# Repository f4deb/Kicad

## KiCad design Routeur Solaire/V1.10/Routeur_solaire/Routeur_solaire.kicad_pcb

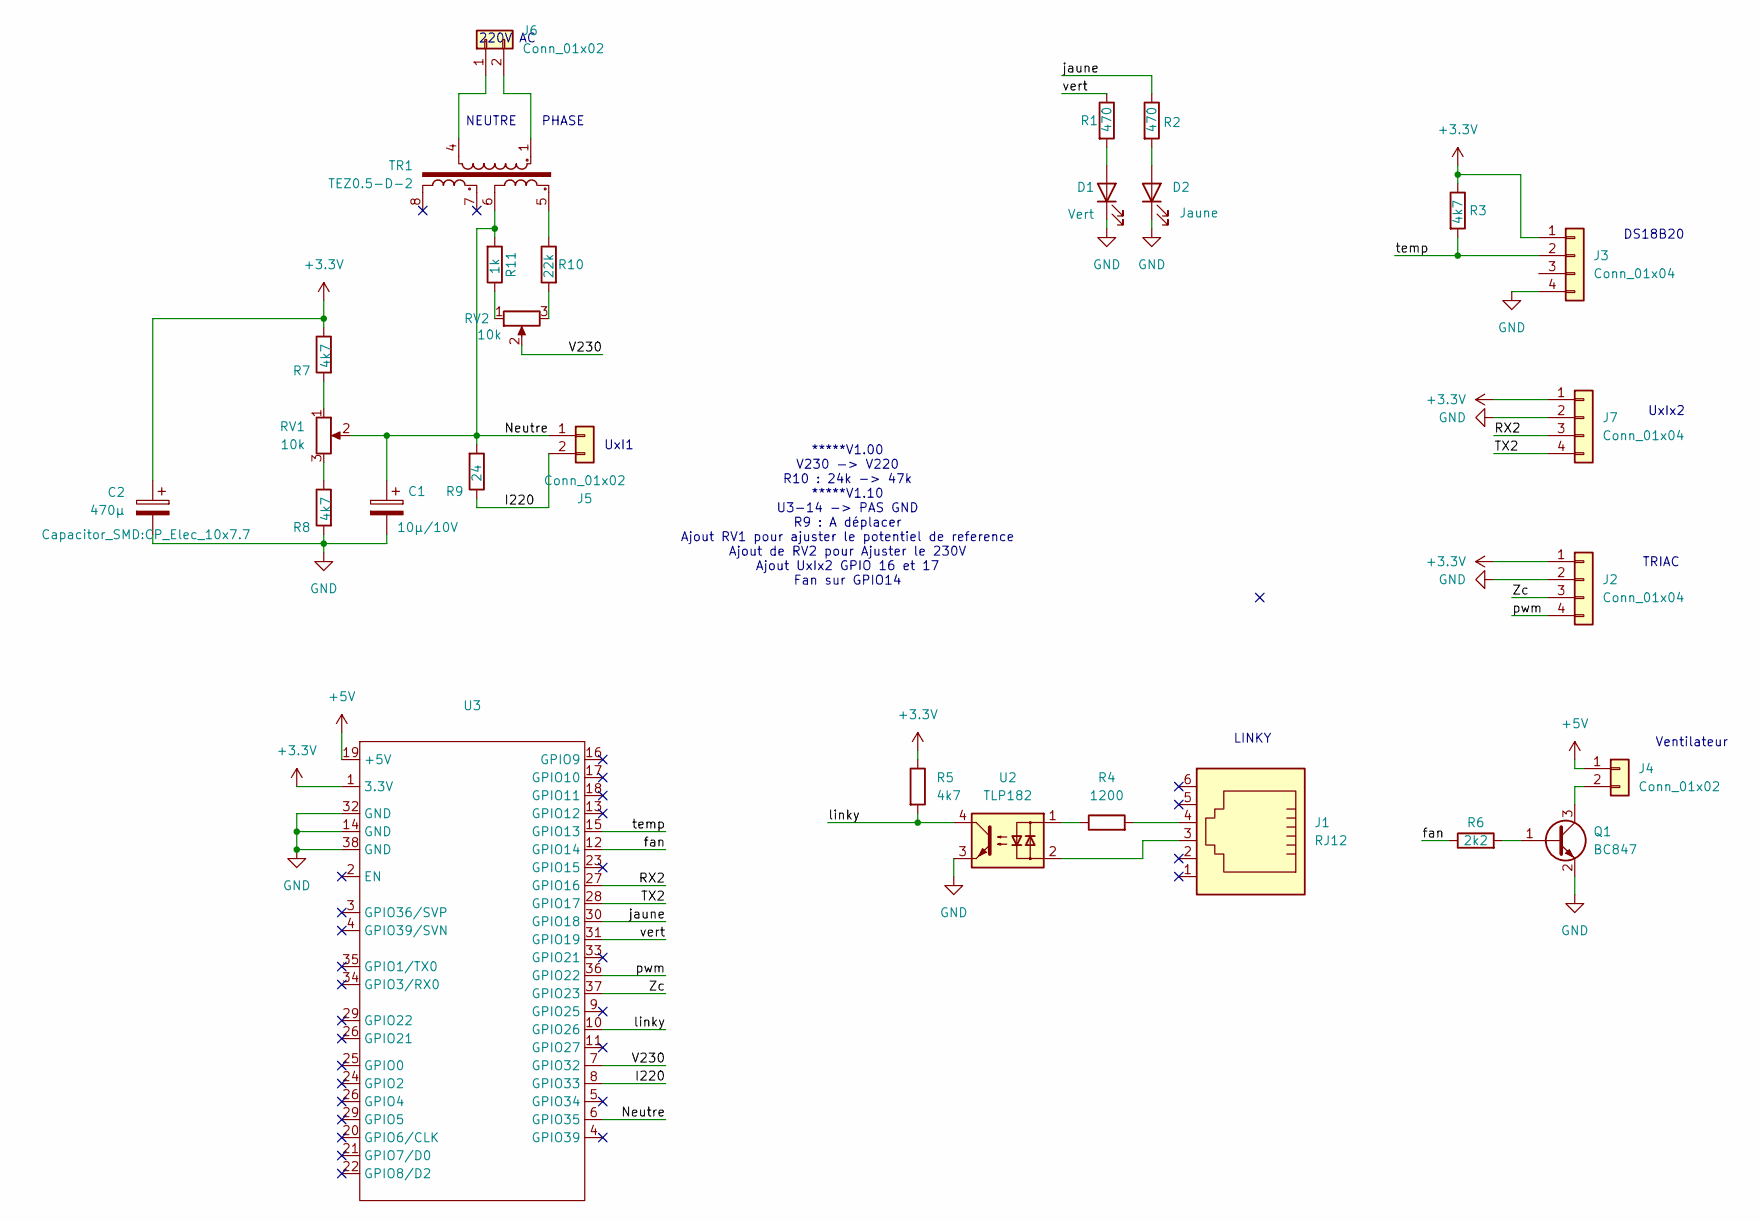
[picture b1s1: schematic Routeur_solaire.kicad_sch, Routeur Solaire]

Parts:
C1: 10µ/10V; CP_Elec_6.3x3
C2: 470µ; CP_Elec_10x7.7
D1: Vert; LED_0805_2012Metric_Pad1.15x1.40mm_HandSolder
D2: Jaune; LED_0805_2012Metric_Pad1.15x1.40mm_HandSolder
J1: RJ12; RJ25_Wayconn_MJEA-660X1_Horizontal
J2, J3, J7: Conn_01x04; PhoenixContact_MCV_1,5_4-G-3.81_1x04_P3.81mm_Vertical
J4, J5: Conn_01x02; PhoenixContact_MCV_1,5_2-G-3.81_1x02_P3.81mm_Vertical
J6: Conn_01x02; PhoenixContact_MSTBVA_2,5_2-G-5,08_1x02_P5.08mm_Vertical
Q1: BC847; SOT-23
R1, R2: 470; R_0603_1608Metric_Pad0.98x0.95mm_HandSolder
R3, R5: 4k7; R_0603_1608Metric_Pad0.98x0.95mm_HandSolder
R4: 1200; R_0805_2012Metric_Pad1.20x1.40mm_HandSolder
R6: 2k2; R_0603_1608Metric_Pad0.98x0.95mm_HandSolder
R7, R8: 4k7; R_0805_2012Metric_Pad1.20x1.40mm_HandSolder
R9: 24; R_0805_2012Metric_Pad1.20x1.40mm_HandSolder
R10: 22k; R_0805_2012Metric_Pad1.20x1.40mm_HandSolder
R11: 1k; R_0805_2012Metric_Pad1.20x1.40mm_HandSolder
RV1, RV2: 10k; Potentiometer_Bourns_3269W_Vertical
TR1: TEZ0.5-D-2; Transformer_Breve_TEZ-22x24
U2: TLP182; SO-4_4.4x3.9mm_P2.54mm
U3: ESP32-DEV-KIT-V4

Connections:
+3.3V: C2.1, J2.1, J3.1, J7.1, R3.1, R5.1, R7.1, U3.1 (3.3V)
+5V: J4.1, U3.19 (+5V)
/I220: J5.2, R9.1, U3.8 (GPIO33)
/Neutre: C1.1, J5.1, R9.2, R11.2, RV1.2, TR1.6, U3.6 (GPIO35)
/RX2: J7.3, U3.27 (GPIO16)
/TX2: J7.4, U3.28 (GPIO17)
/V230: RV2.2, U3.7 (GPIO32)
/Zc: J2.3, U3.37 (GPIO23)
/fan: R6.1, U3.12 (GPIO14)
/jaune: R2.1, U3.30 (GPIO18)
/linky: R5.2, U2.4, U3.10 (GPIO26)
/pwm: J2.4, U3.36 (GPIO22)
/temp: J3.2, R3.2, U3.15 (GPIO13)
/vert: R1.1, U3.31 (GPIO19)
GND: C1.2, C2.2, D1.1 (K), D2.1 (K), J2.2, J3.4, J7.2, Q1.2 (E), R8.2, U2.3, U3.14 (GND), U3.32 (GND), U3.38 (GND)
unnamed: D1.2 (A), R1.2
unnamed: D2.2 (A), R2.2
unnamed: J1.3, U2.2
unnamed: J1.4, R4.2
unnamed: J4.2, Q1.3 (C)
unnamed: J6.1, TR1.4
unnamed: J6.2, TR1.1
unnamed: Q1.1 (B), R6.2
unnamed: R4.1, U2.1
unnamed: R7.2, RV1.1
unnamed: R8.1, RV1.3
unnamed: R10.1, TR1.5
unnamed: R10.2, RV2.3
unnamed: R11.1, RV2.1

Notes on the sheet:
TRIAC
PHASE
NEUTRE
LINKY
UxIx2
UxI1
*****V1.00 V230 -> V220 R10 : 24k -> 47k *****V1.10 U3-14 -> PAS GND R9 : A déplacer Ajout RV1 pour ajuster le potentiel de reference Ajout de RV2 pour Ajuster le 230V Ajout UxIx2 GPIO 16 et 17 Fan sur GPIO14
DS18B20
Ventilateur
220V AC

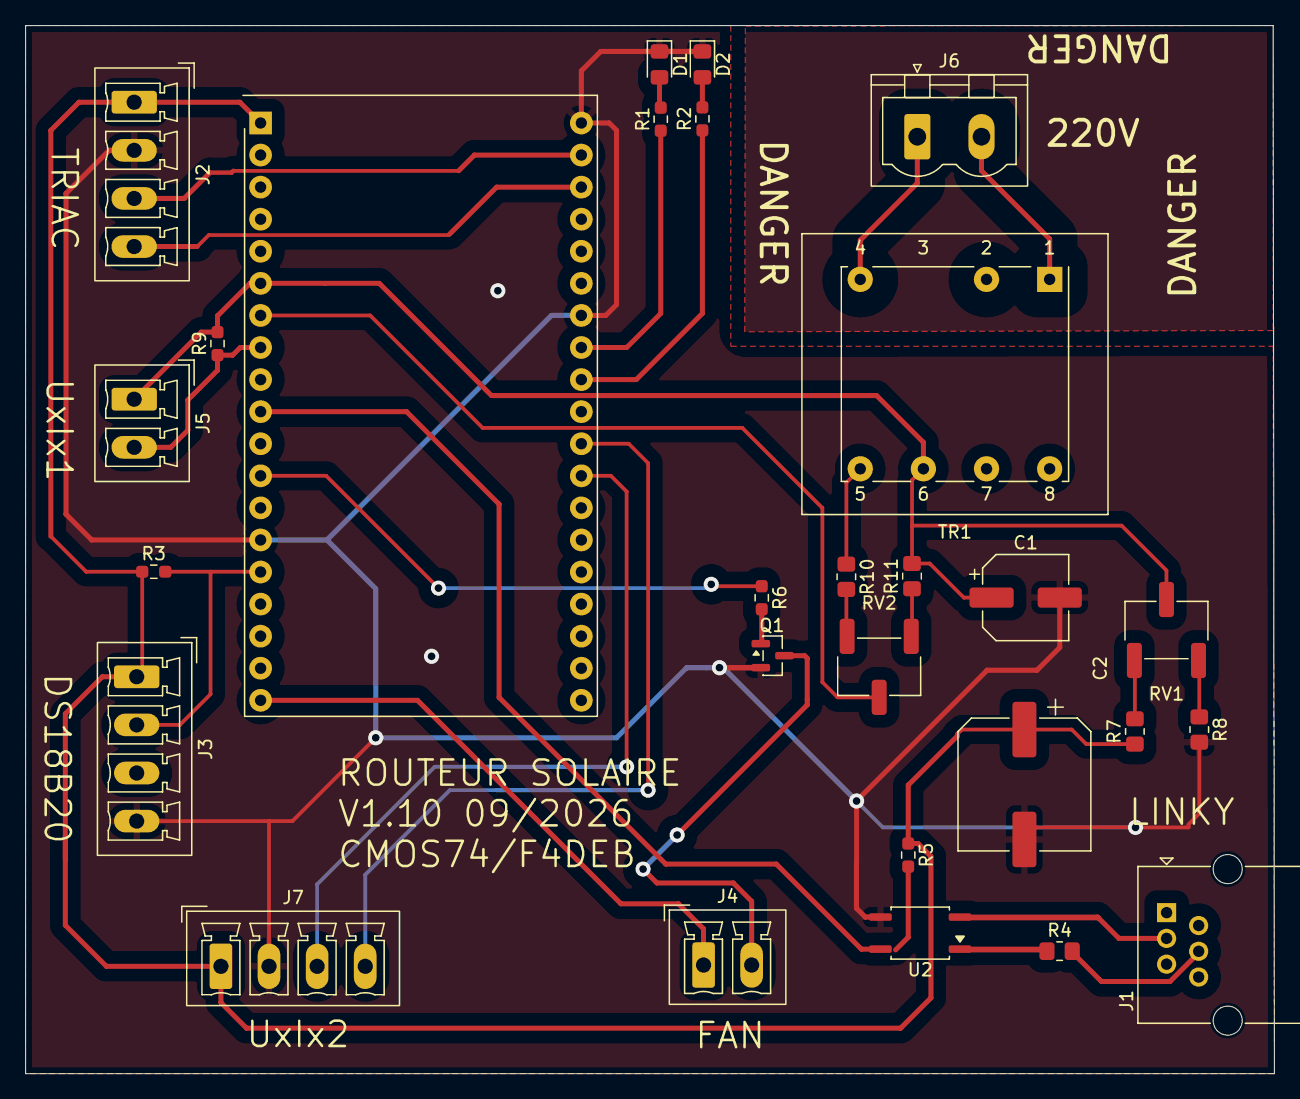
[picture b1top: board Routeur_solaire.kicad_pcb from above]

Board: 2 copper layers, 98.9 x 83.0 mm, 28 parts (0 on the bottom side), 29 nets.

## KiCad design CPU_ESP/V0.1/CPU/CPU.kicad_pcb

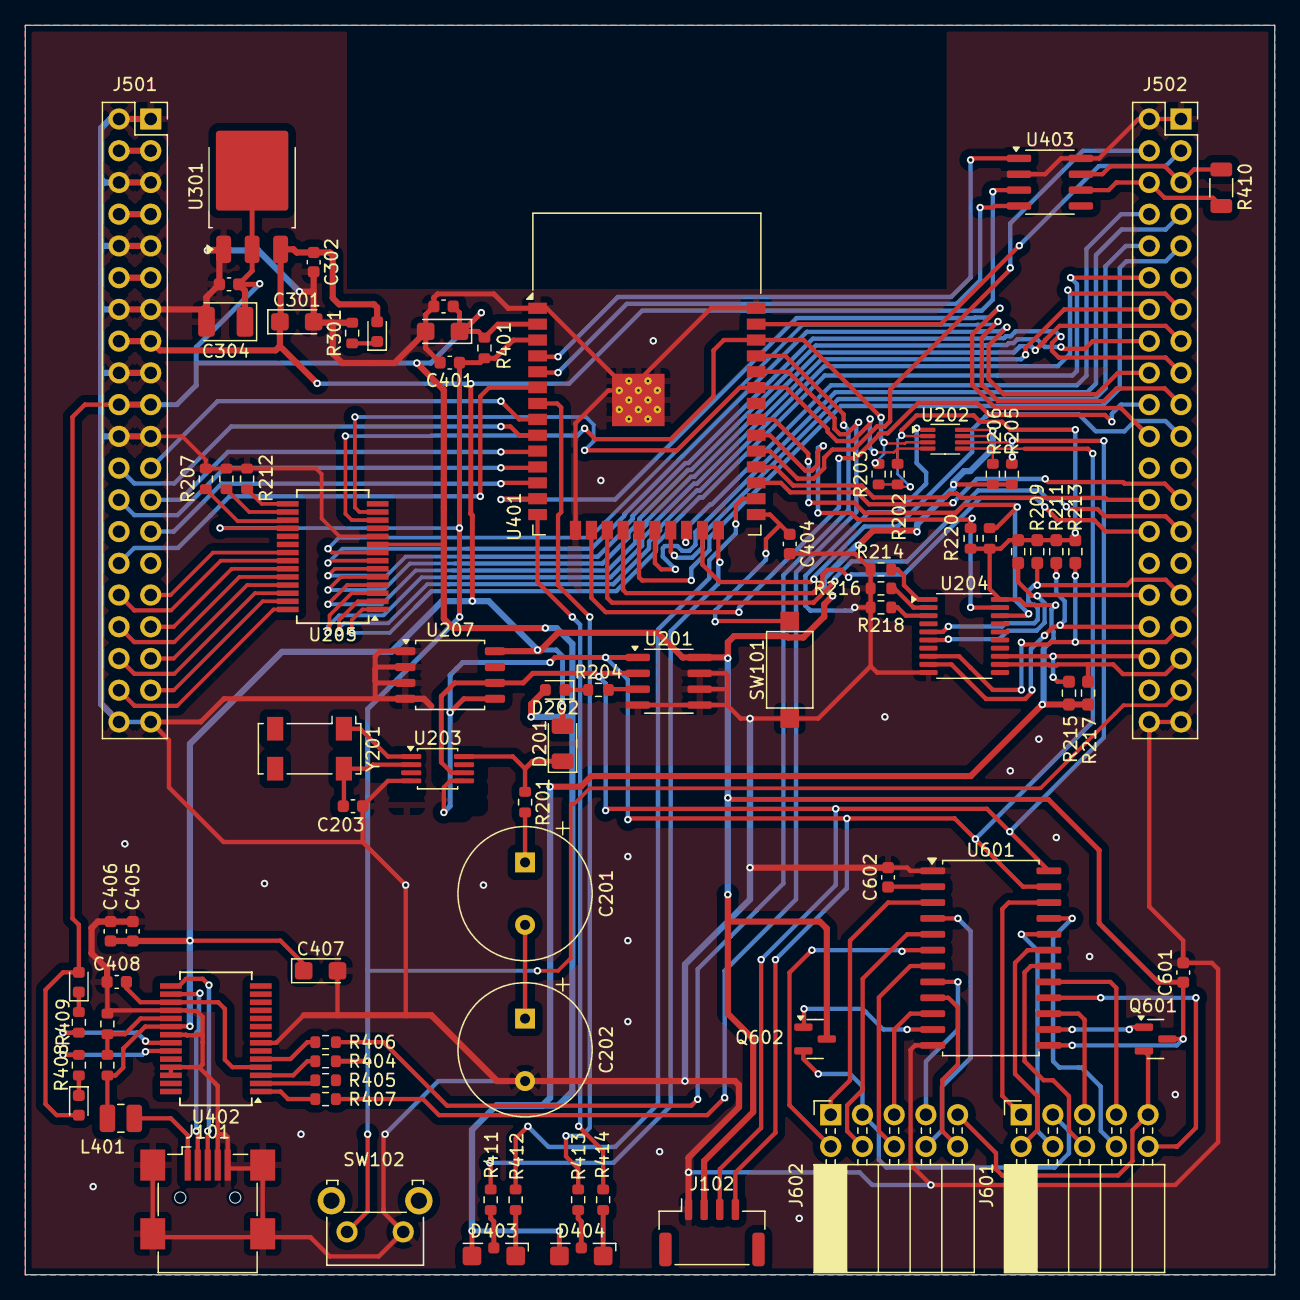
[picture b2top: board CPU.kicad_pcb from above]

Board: 2 copper layers, 100.0 x 100.0 mm, 82 parts (0 on the bottom side), 117 nets.

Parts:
C201, C202: 10F/2.7V; CP_Radial_Tantal_D10.5mm_P5.00mm
C203: 10n; C_0603_1608Metric
C301: 22µ; CP_EIA-3216-10_Kemet-I
C302, C303, C401, C403, C404, C405, C406, C408, C601: 100n; C_0603_1608Metric
C304: 22µ; CP_EIA-3528-21_Kemet-B
C402: 22µ/10V; CP_EIA-3216-10_Kemet-I
C407: 4.7µ/10V; CP_EIA-3216-12_Kemet-S
C602: 2.7n; C_0603_1608Metric
D201: D_Schottky; D_1206_3216Metric
D202: RED; LED_0603_1608Metric
D301: RED LED; LED_0603_1608Metric
D401, D402: ORANGE; LED_0603_1608Metric
D403, D404: LED_Dual_KAK; LED_Kingbright_KPA-3010_3x2x1mm
J101: USB_B_Mini; USB_Mini-B_Wuerth_65100516121_Horizontal
J102: Conn_01x04; JST_GH_SM04B-GHS-TB_1x04-1MP_P1.25mm_Horizontal
J501, J502: Conn_02x20_Odd_Even; PinSocket_2x20_P2.54mm_Vertical
J601, J602: PinSocket_2x05_P2.54mm_Horizontal
L401: 22µ; L_1008_2520Metric
Q601, Q602: BSR19; SOT-23
R201: 150; R_0603_1608Metric
R202, R203, R205, R206: 2.2K; R_0603_1608Metric
R204, R411, R412, R413, R414: 330; R_0603_1608Metric
R207, R210, R212, R214, R216, R218, R404, R406, R407: 0; R_0603_1608Metric
R208, R209, R211, R213, R215, R217: 2k2; R_0603_1608Metric_Pad0.98x0.95mm_HandSolder
R219, R220, R402, R403: 2k2; R_0603_1608Metric
R301: 2K; R_0603_1608Metric
R401: 10k; R_0603_1608Metric
R405: NC; R_0603_1608Metric
R408, R409: 4k7; R_0603_1608Metric
R410: 120; R_1206_3216Metric
SW101: SW_Push_45deg; SW_SPST_CK_RS282G05A3
SW102: SW_Push_45deg; SW_Tactile_SKHH_Angled
U201: LM75A; SOIC-8_3.9x4.9mm_P1.27mm
U202: PCA9306; VSSOP-8_2.3x2mm_P0.5mm
U203: PCF8563T; MSOP-8_3x3mm_P0.65mm
U204: TCA9544A; TSSOP-20_4.4x6.5mm_P0.65mm
U205: MCP23017_SS; SSOP-28_5.3x10.2mm_P0.65mm
U207: AT24CS01-SSHM; SOIC-8_5.3x5.3mm_P1.27mm
U301: LM1117DT-2.5; TO-252-3_TabPin2
U401: ESP32-WROOM-32
U402: FT232RL; SSOP-28_5.3x10.2mm_P0.65mm
U403: TJA1051T; SOIC-8_3.9x4.9mm_P1.27mm
U601: SAA1064T; SOP-24_7.5x15.4mm_P1.27mm
Y201: 32.278kHz; Crystal_SMD_Abracon_ABS25-4Pin_8.0x3.8mm

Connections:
+3.3V: C303.1, C304.1, C402.1, C403.1, D202.2 (A), D401.2 (A), D402.2 (A), D403.2 (A), D404.2 (A), J501.19, J501.20, R202.1, R203.1, R208.1, R209.1, R211.1, R213.1, R215.1, R217.1, R219.1, R220.1, R401.2, U202.2 (VREF1), U204.20 (VCC), U205.9 (VDD), U301.2 (VO), U401.2 (VDD)
+5VA: J501.11, J501.12
+5VD: C301.1, C302.1, C405.1, C406.1, C407.1, C601.1, D201.2 (A), D301.2 (A), J102.2, J501.15, J501.16, L401.2, Q601.3 (C), Q602.3 (C), R205.1, R206.1, R403.1, U201.8 (+Vs), U202.7 (VREF2), U202.8 (EN), U207.8 (VCC), U301.3 (VI), U402.20 (VCC), U403.3 (VCC), U601.13 (VCC)
+12V: J501.7, J501.8
+BATT: J501.3, J501.4
/CANH: J502.5, R410.2, U403.7 (CANH)
/CANL: J502.6, R410.1, U403.6 (CANL)
/D0: J502.12, U205.1 (GPB0)
/D1: J502.13, U205.2 (GPB1)
/D2: J502.14, U205.3 (GPB2)
/D3: J502.15, U205.4 (GPB3)
/D4: J502.16, U205.5 (GPB4)
/D5: J502.17, U205.6 (GPB5)
/D6: J502.18, U205.7 (GPB6)
/D7: J502.19, U205.8 (GPB7)
/E: J502.20, U401.16 (IO13)
/ESP32 Module/BOOT: C404.1, SW101.2, U401.25 (IO0)
/ESP32 Module/CAN-RX: U401.5 (SENSOR_VN), U403.4 (RXD)
/ESP32 Module/CAN-TX: U401.4 (SENSOR_VP), U403.1 (TXD)
/ESP32 Module/D+: J101.3 (D+), U402.15 (USBD+)
/ESP32 Module/D-: J101.2 (D-), U402.16 (USBD-)
/ESP32 Module/VCCUSB: J101.1 (VBUS), L401.1
/IO0: J501.31, U205.21 (GPA0)
/IO1: J501.32, U205.22 (GPA1)
/IO2: J501.33, U205.23 (GPA2)
/IO3: J501.34, U205.24 (GPA3)
/IO4: J501.35, U205.25 (GPA4)
/IO5: J501.36, U205.26 (GPA5)
/IO6: J501.37, U205.27 (GPA6)
/IO7: J501.38, U205.28 (GPA7)
/IO8: J501.30, U401.6 (IO34)
/PWM0: J501.23, U401.8 (IO32)
/PWM1: J501.24, U401.9 (IO33)
/PWM2: J501.25, U401.10 (IO25)
/PWM3: J501.26, U401.11 (IO26)
/PWM4: J501.27, U401.12 (IO27)
/RESET: C401.1, J502.37, R401.1, R404.2, SW102.2, U205.18 (~RESET), U401.3 (EN)
/RS: J502.21, U401.23 (IO15)
/RW: J502.22, U401.13 (IO14)
/RX0: R407.2, U401.34 (RXD0/IO3)
/RX1: J502.25, U401.27 (IO16)
/RX2: J502.27, U401.17 (SHD/SD2)
/SCK: J502.7, U401.20 (SCK/CLK)
/SCL: R203.2, U202.3 (SCL1), U205.12 (SCK), U401.36 (IO22)
/SCL0-E: J502.32, R208.2, U204.6 (SC0)
/SCL1: R219.2, U204.18 (SCL), U401.31 (IO19)
/SCL1-E: J502.34, R211.2, U204.9 (SC1)
/SCL2-E: J502.36, R215.2, U204.13 (SC2)
/SCL-5V: J102.3, R205.2, U201.2 (SCL), U202.6 (SCL2), U203.6 (SCL), U207.6 (SCL), U601.24 (SCL)
/SCS: J502.9, U401.19 (SCS/CMD)
/SDA: R202.2, U202.4 (SDA1), U205.13 (SDA), U401.33 (IO21)
/SDA0-E: J502.31, R209.2, U204.5 (SD0)
/SDA1: R220.2, U204.19 (SDA), U401.30 (IO18)
/SDA1-E: J502.33, R213.2, U204.8 (SD1)
/SDA2-E: J502.35, R217.2, U204.12 (SD2)
/SDA-5V: J102.4, R206.2, U201.1 (SDA), U202.5 (SDA2), U203.5 (SDA), U207.5 (SDA), U601.23 (SDA)
/SDI: J502.8, U401.22 (SDI/SD1)
/SDO: J502.10, U401.21 (SDO/SD0)
/SEVEN SEGMENTS/A34: J601.7, U601.17 (P11)
/SEVEN SEGMENTS/B34: J601.5, U601.15 (P9)
/SEVEN SEGMENTS/C34: J601.6, U601.18 (P12)
/SEVEN SEGMENTS/D34: J601.4, U601.20 (P14)
/SEVEN SEGMENTS/E34: J601.2, U601.19 (P13)
/SEVEN SEGMENTS/F34: J601.1, U601.22 (P16)
/SEVEN SEGMENTS/G34: J601.8, U601.21 (P15)
/SEVEN SEGMENTS/P34: J601.10, U601.16 (P10)
/T1CK: J502.3, U401.37 (IO23)
/T2CK: J502.4, U401.29 (IO5)
/TX0: R406.2, U401.35 (TXD0/IO1)
/TX1: J502.26, U401.28 (IO17)
/TX2: J502.28, U401.18 (SWP/SD3)
GND: C202.2, C203.2, C301.2, C302.2, C303.2, C304.2, C401.2, C402.2, C403.2, C404.2, C405.2, C406.2, C407.2, C408.1, C601.2, C602.2, J101.4 (ID), J101.5 (GND), J101.6 (Shield), J102.1, J501.1, J501.2, J501.5, J501.6, J501.9, J501.10, J501.13, J501.14, J501.17, J501.18, J501.21, J501.22, J501.39, J501.40, J502.1, J502.2, J502.39, J502.40, R207.2, R210.2, R212.2, R214.2, R216.2, R218.2, R301.2, R402.2, SW101.1, SW102.1, U201.4 (GND), U201.5 (A2), U201.6 (A1), U201.7 (A0), U202.1 (GND), U203.4 (VSS), U204.10 (GND), U205.10 (VSS), U207.1 (A0), U207.2 (A1), U207.3 (A2), U207.4 (GND), U301.1 (GND), U401.1 (GND), U401.15 (GND), U401.38 (GND), U401.39 (GND), U402.7 (GND), U402.18 (GND), U402.21 (GND), U402.25 (AGND), U402.26 (TEST), U403.2 (GND), U403.8 (S), U601.1 (ADR), U601.12 (VSS)
unnamed: C201.1, R201.2
unnamed: C201.2, C202.1
unnamed: D201.1 (K), R201.1, U203.8 (VDD)
unnamed: D202.1 (K), R204.1
unnamed: D301.1 (K), R301.1
unnamed: D401.1 (K), R408.2
unnamed: D402.1 (K), R409.2
unnamed: D403.1 (K1), R412.1
unnamed: D403.3 (K2), R411.1
unnamed: D404.1 (K1), R414.1
unnamed: D404.3 (K2), R413.1
unnamed: J601.3, J602.3, Q602.2 (E)
unnamed: J601.9, J602.9, Q601.2 (E)
unnamed: J602.1, U601.3 (P8)
unnamed: J602.2, U601.6 (P5)
unnamed: J602.4, U601.5 (P6)
unnamed: J602.5, U601.10 (P1)
unnamed: J602.6, U601.7 (P4)
unnamed: J602.7, U601.8 (P3)
unnamed: J602.8, U601.4 (P7)
unnamed: J602.10, U601.9 (P2)
unnamed: Q601.1 (B), U601.14 (MX2)
unnamed: Q602.1 (B), U601.11 (MX1)
unnamed: R204.2, U201.3 (O.S.)
unnamed: U203.1 (OSCI), Y201.1
unnamed: C203.1, U203.2 (OSCO), Y201.4
unnamed: R214.1, U204.1 (A0)
unnamed: R216.1, U204.2 (A1)
unnamed: R218.1, U204.3 (A2)
unnamed: R212.1, U205.15 (A0)
unnamed: R210.1, U205.16 (A1)
unnamed: R207.1, U205.17 (A2)
unnamed: R411.2, U401.24 (IO2)
unnamed: R412.2, U401.26 (IO4)
unnamed: R414.2, U401.14 (IO12)
unnamed: R413.2, U401.7 (IO35)
unnamed: C408.2, U402.4 (VCCIO), U402.17 (3V3OUT)
unnamed: R408.1, U402.23 (CBUS0)
unnamed: R409.1, U402.22 (CBUS1)
unnamed: R405.1, U402.2 (DTR)
unnamed: R404.1, U402.3 (RTS)
unnamed: R406.1, U402.5 (RXD)
unnamed: R407.1, U402.1 (TXD)
unnamed: R402.1, R403.2, U402.19 (~RESET)
unnamed: C602.1, U601.2 (CEXT)

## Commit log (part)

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2026-05-12 Init
2026-06-05 Update I2C Adresse
